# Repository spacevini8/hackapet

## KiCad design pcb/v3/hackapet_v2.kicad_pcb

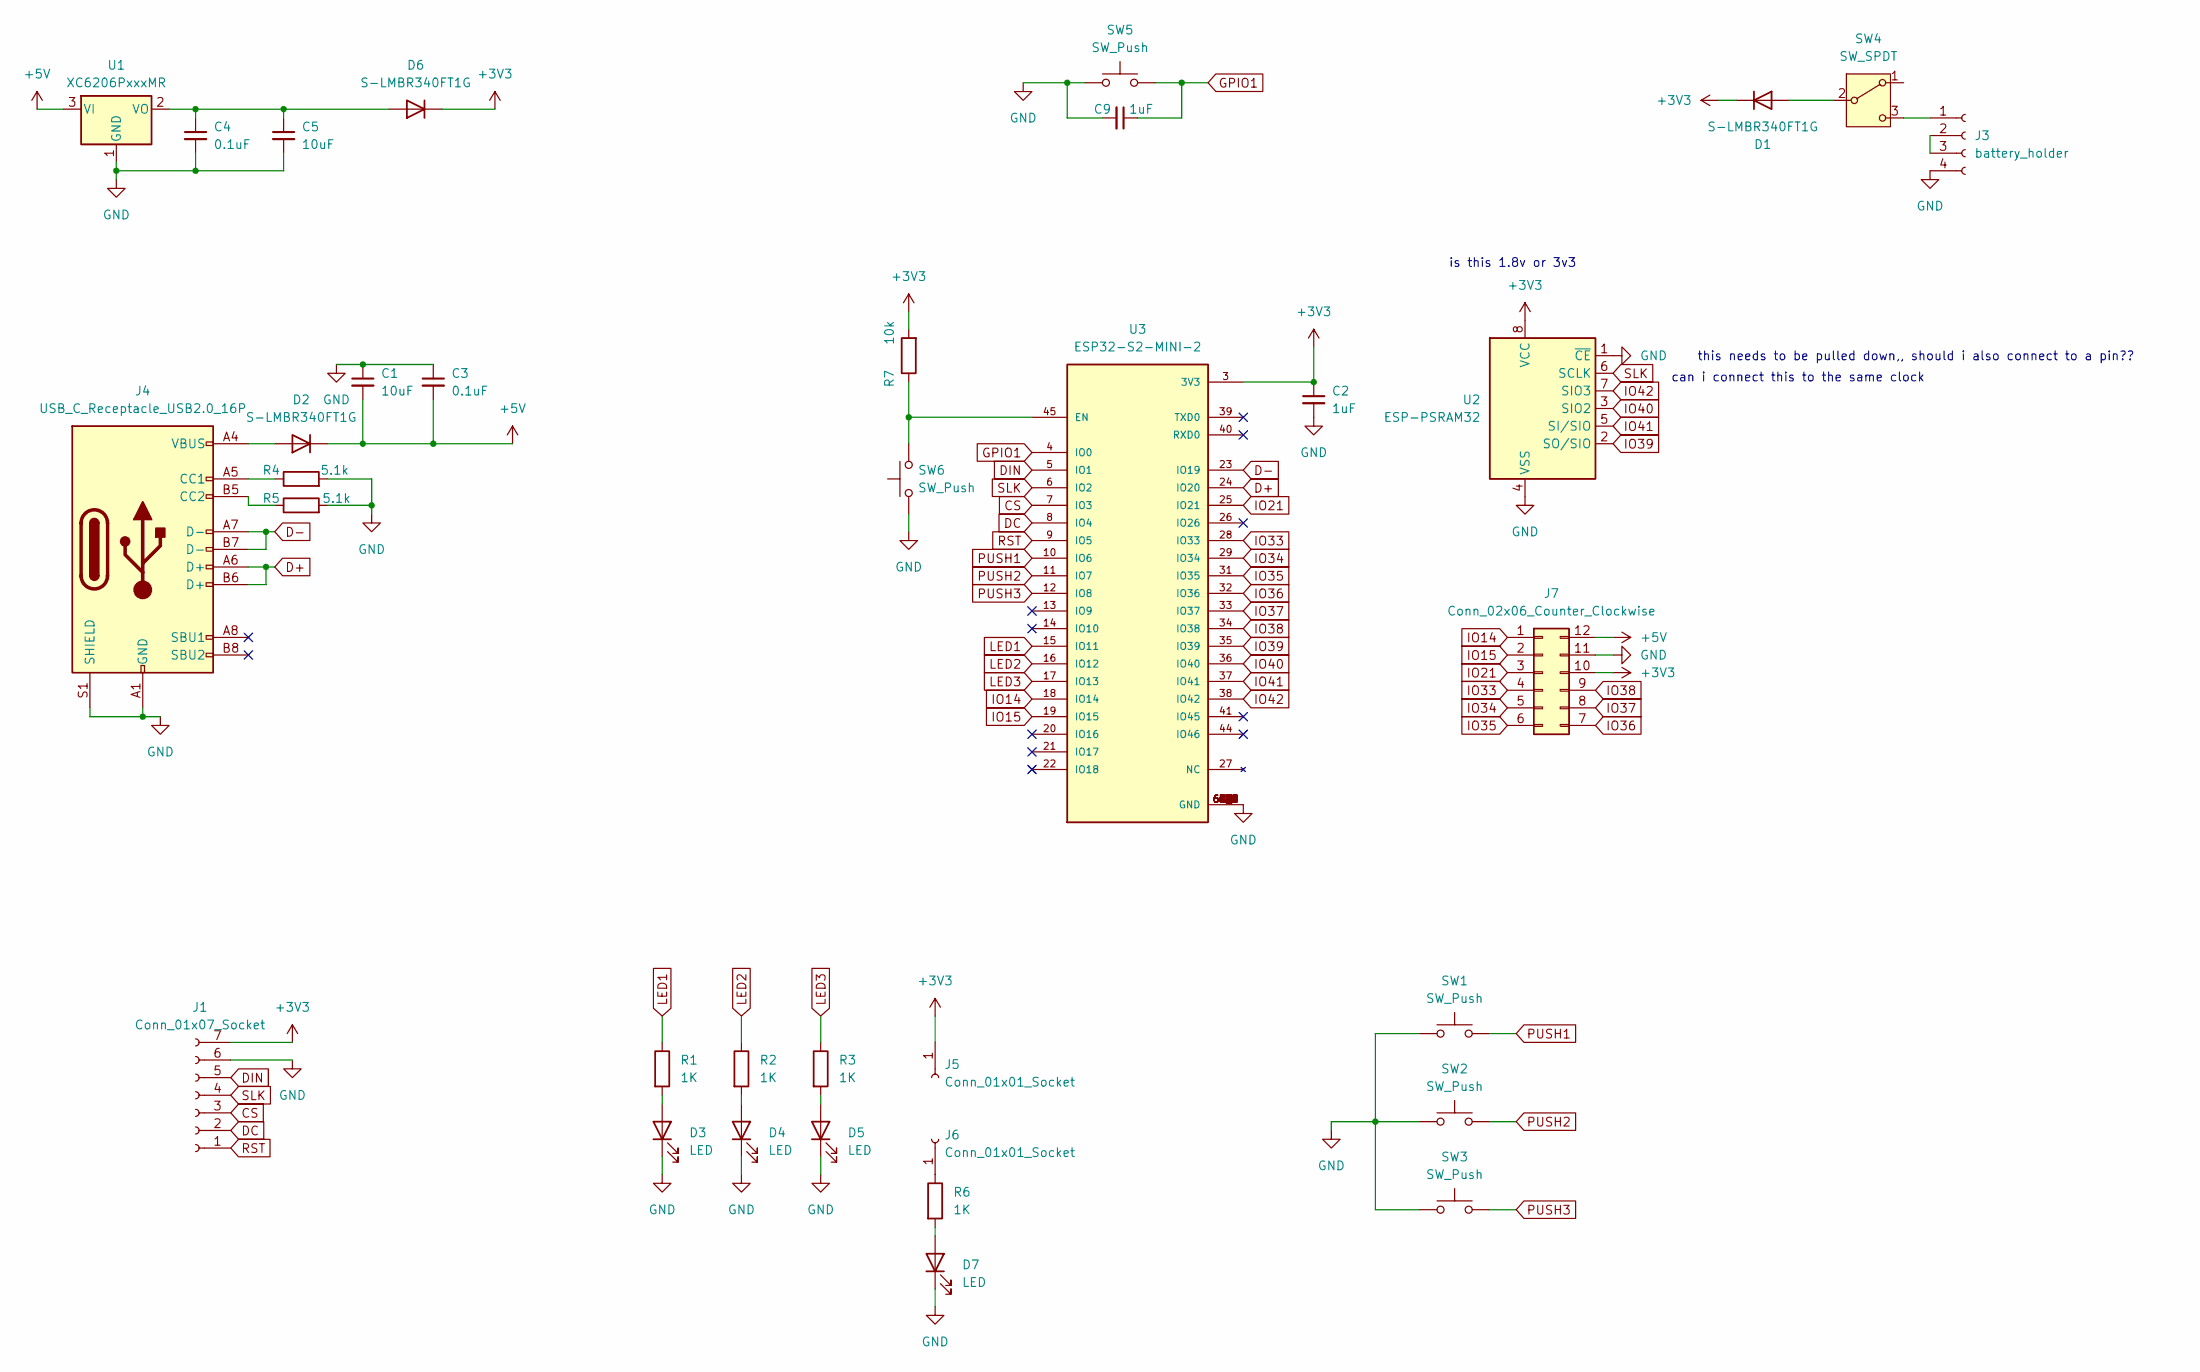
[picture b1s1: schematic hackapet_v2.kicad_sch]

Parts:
C1, C5: 10uF; C_0805_2012Metric; LCSC C5189822
C2, C9: 1uF; C_0805_2012Metric; LCSC C215803
C3, C4: 0.1uF; C_0805_2012Metric; LCSC C28378
D1, D2, D6: S-LMBR340FT1G; D_0805_2012Metric; LCSC C2972823
D3, D4, D5, D7: LED; LED_0805_2012Metric
J1: Conn_01x07_Socket; PinSocket_1x07_P2.54mm_Vertical; LCSC C22438073
J3: battery_holder; 1022_batteryholder
J4: USB_C_Receptacle_USB2.0_16P; USB_C_Receptacle_HCTL_HC-TYPE-C-16P-01A; LCSC C393939
J5, J6: Conn_01x01_Socket; PinSocket_1x01_P2.54mm_Vertical
J7: Conn_02x06_Counter_Clockwise; PinSocket_2x06_P2.54mm_Vertical
R1, R2, R3, R6: 1K; R_0805_2012Metric; LCSC C17513
R4, R5: 5.1k; R_0805_2012Metric; LCSC C104375
R7: 10k; R_0402_1005Metric
SW1, SW2, SW3: SW_Push; SW_Push_1P1T_NO_6x6mm_H9.5mm; LCSC C381038
SW4: SW_SPDT; SW_DPDT_CK_JS202011JCQN; LCSC C221666
SW5: SW_Push; SW_Push_1P1T_XKB_TS-1187A; LCSC C381038
SW6: SW_Push; SW_Push_1P1T_XKB_TS-1187A
U1: XC6206PxxxMR; SOT-23-3
U2: ESP-PSRAM32; SOIC-8_3.9x4.9mm_P1.27mm
U3: ESP32-S2-MINI-2; XCVR_ESP32-S2-MINI-1; PARTREV 1.0; LCSC C3013906

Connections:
+3V3: C2.1, D1.1 (K), D6.1 (K), J1.7, J5.1, J7.10, R7.2, U2.8 (VCC), U3.3 (3V3)
+5V: C1.2, C3.2, D2.1 (K), J7.12, U1.3 (VI)
CS: J1.3, U3.7 (IO3)
D+: J4.A6 (D+), J4.B6 (D+), U3.24 (IO20)
D-: J4.A7 (D-), J4.B7 (D-), U3.23 (IO19)
DC: J1.2, U3.8 (IO4)
DIN: J1.5, U3.5 (IO1)
GND: C1.1, C2.2, C3.1, C4.2, C5.2, C9.2, D3.1 (K), D4.1 (K), D5.1 (K), D7.1 (K), J1.6, J3.4, J4.A1 (GND), J4.A12 (GND), J4.B1 (GND), J4.B12 (GND), J4.S1 (SHIELD), J7.11, R4.2, R5.2, SW1.1, SW2.1, SW3.1, SW5.1, SW6.1, U1.1 (GND), U2.1 (~CE), U2.4 (VSS), U3.1 (GND), U3.2 (GND), U3.30 (GND), U3.42 (GND), U3.43 (GND), U3.46 (GND), U3.47 (GND), U3.48 (GND), U3.49 (GND), U3.50 (GND), U3.51 (GND), U3.52 (GND), U3.53 (GND), U3.54 (GND), U3.55 (GND), U3.56 (GND), U3.57 (GND), U3.58 (GND), U3.59 (GND), U3.60 (GND), U3.61 (GND), U3.61_1 (GND), U3.61_2 (GND), U3.61_3 (GND), U3.61_4 (GND), U3.61_5 (GND), U3.61_6 (GND), U3.61_7 (GND), U3.61_8 (GND), U3.62 (GND), U3.63 (GND), U3.64 (GND), U3.65 (GND)
GPIO1: C9.1, SW5.2, U3.4 (IO0)
IO14: J7.1, U3.18 (IO14)
IO15: J7.2, U3.19 (IO15)
IO21: J7.3, U3.25 (IO21)
IO33: J7.4, U3.28 (IO33)
IO34: J7.5, U3.29 (IO34)
IO35: J7.6, U3.31 (IO35)
IO36: J7.7, U3.32 (IO36)
IO37: J7.8, U3.33 (IO37)
IO38: J7.9, U3.34 (IO38)
IO39: U2.2 (SO/SIO), U3.35 (IO39)
IO40: U2.3 (SIO2), U3.36 (IO40)
IO41: U2.5 (SI/SIO), U3.37 (IO41)
IO42: U2.7 (SIO3), U3.38 (IO42)
LED1: R1.1, U3.15 (IO11)
LED2: R2.1, U3.16 (IO12)
LED3: R3.1, U3.17 (IO13)
unnamed: D1.2 (A), SW4.2 (B)
unnamed: D2.2 (A), J4.A4 (VBUS), J4.A9 (VBUS), J4.B4 (VBUS), J4.B9 (VBUS)
unnamed: D3.2 (A), R1.2
unnamed: D4.2 (A), R2.2
unnamed: D5.2 (A), R3.2
unnamed: C4.1, C5.1, D6.2 (A), U1.2 (VO)
unnamed: D7.2 (A), R6.2
unnamed: J3.1, SW4.3 (C)
unnamed: J3.2, J3.3
unnamed: J4.A5 (CC1), R4.1
unnamed: J4.B5 (CC2), R5.1
unnamed: J6.1, R6.1
unnamed: R7.1, SW6.2, U3.45 (EN)
PUSH1: SW1.2, U3.10 (IO6)
PUSH2: SW2.2, U3.11 (IO7)
PUSH3: SW3.2, U3.12 (IO8)
RST: J1.1, U3.9 (IO5)
SLK: J1.4, U2.6 (SCLK), U3.6 (IO2)

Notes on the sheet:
this needs to be pulled down,, should i also connect to a pin??
can i connect this to the same clock
is this 1.8v or 3v3

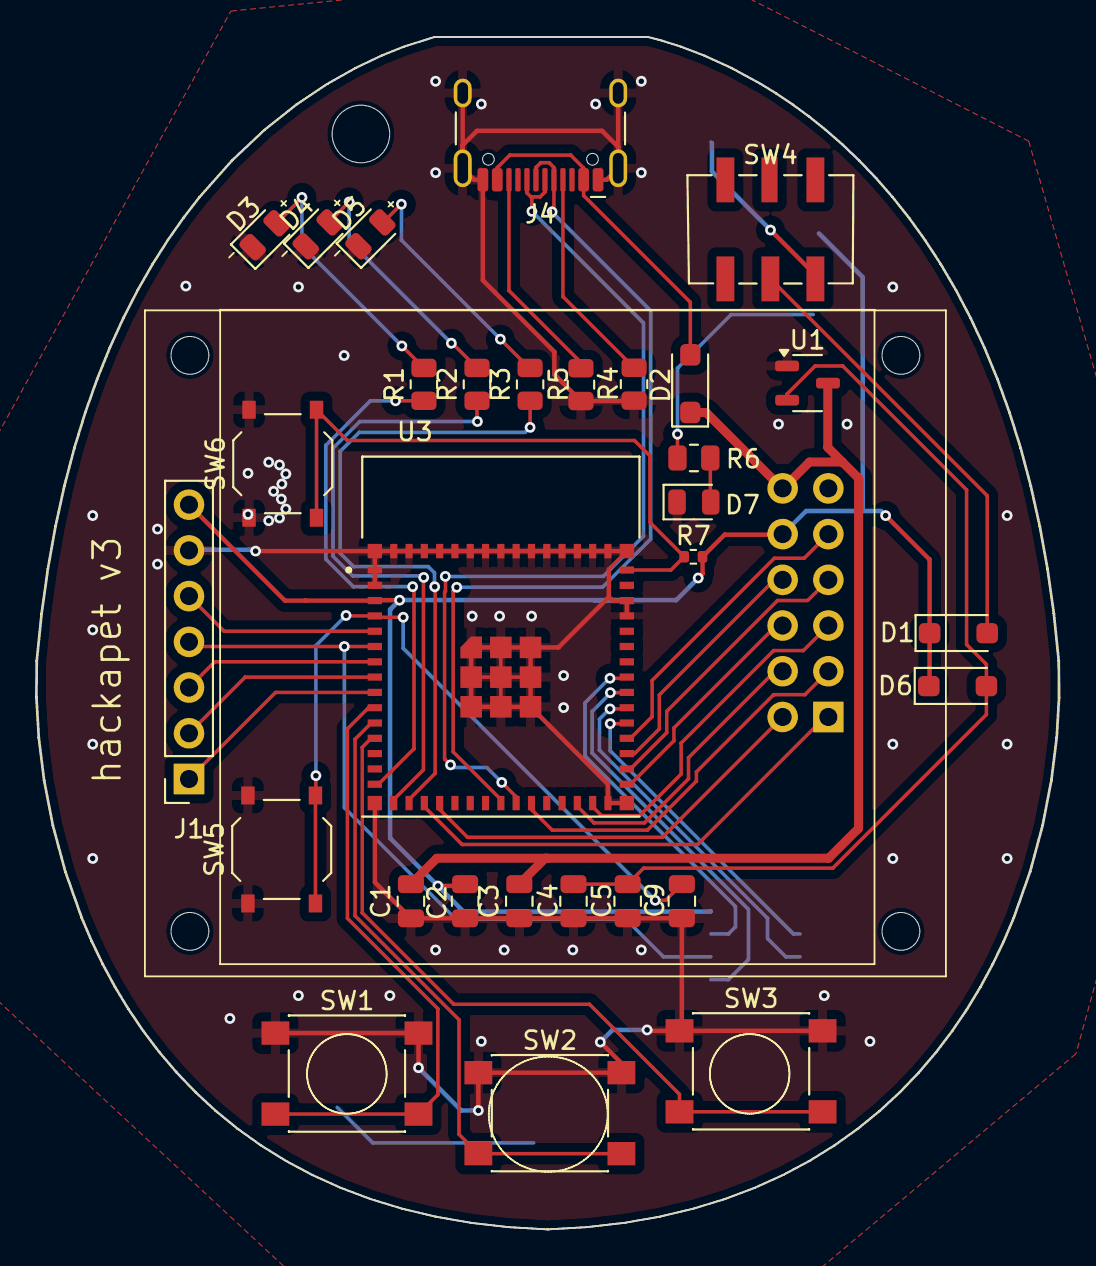
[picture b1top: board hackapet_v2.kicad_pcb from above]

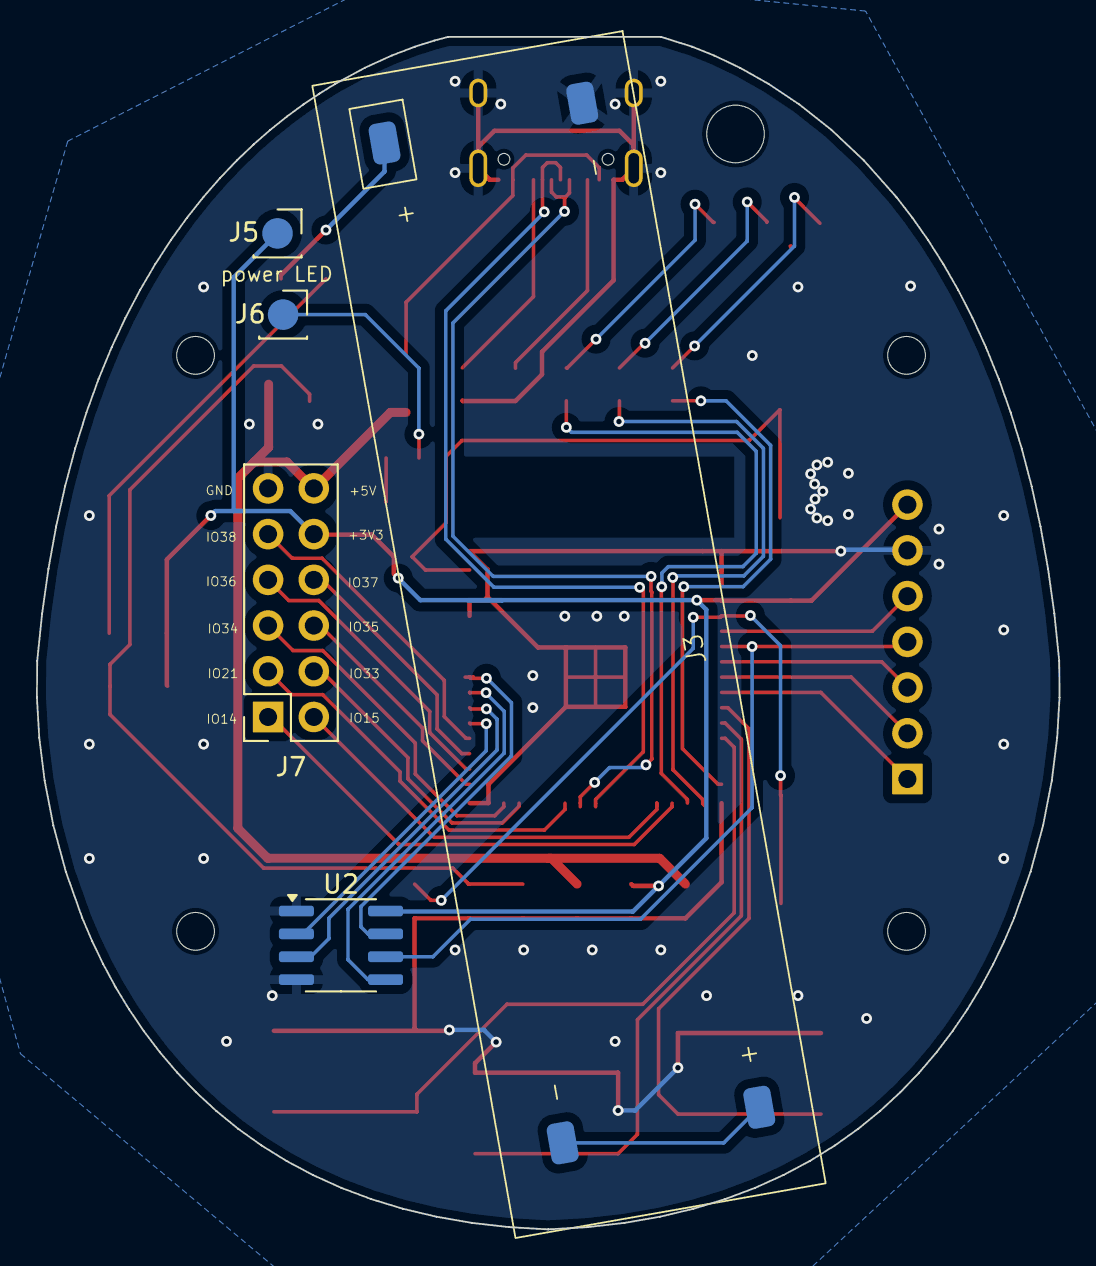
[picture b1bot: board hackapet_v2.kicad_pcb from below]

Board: 2 copper layers, 56.8 x 66.2 mm, 35 parts (5 on the bottom side), 43 nets.

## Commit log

2025-01-19 Create slay or save
2025-01-19 Add files via upload
    added project
2025-01-26 Catch Submission
2025-01-26 Add Glitch Fox: Byte Hunter game
2025-01-27 added requirements.txt
2025-01-28 add cat catch
2025-01-28 teachable blob
2025-01-29 starpet v0.1
2025-01-29 rename to space pet 14
2025-01-29 Add pong clone
2025-01-29 v0.2 added door sprites
2025-01-29 added gitignore
2025-01-29 stops player from going past the left and right walls
2025-01-29 added readme
2025-01-29 update readme 2
2025-01-29 update readme 3
2025-01-29 update readme 4
2025-01-29 add scoring system (prototype) and improve controls in space_pet.py
2025-01-30 WIP: Eeevee
2025-01-30 Add comment and update credits screen
2025-01-30 making an experimental food system
2025-01-30 readme update
2025-01-30 update ball texture and make movement smoother
2025-01-30 Made the base game
    Not super sure I did this right
2025-01-30 fixed a bug in the funny eating moff system fr fr no cap (send help)
2025-01-30 Fixed font error
2025-01-30 Initial Game Commit
    Assets and game code
2025-01-30 Inital Commit
2025-01-30 Added requirements.txt file
2025-01-30 Added basic description and instructions
2025-01-31 fix only 3 burgers spawning (of course it was the one change i didn't test)
2025-01-31 Added death condition anc screen
2025-01-31 Add Game
2025-01-31 add start screen, update end screen text
2025-01-31 Added growth stages
2025-01-31 fixed asset errorj
2025-01-31 Added death, start screen, better bakcground ,and fixed fonts
2025-01-31 finished hunger system, added AME sprites
2025-01-31 added a simple game over system
2025-01-31 added game over system
2025-01-31 not much
2025-01-31 Recommitting Main Code
2025-01-31 Added win condition
2025-02-01 Added heal function and health bar
2025-02-01 added croutonpet
2025-02-01 Added feedback features
    I lowkey think there might be a bug with the arrow and tile collision cuz I swear I pressed the key but I still lost a heart...
2025-02-01 Changed settings and updated readme
2025-02-01 Removed hw_accel flag for compatibility
2025-02-01 upload Your Pocket Arctic Fox game files
2025-02-01 Add files via upload
    that's right, i dont wanna git pull this again
2025-02-01 init commit
2025-02-01 added backgrounds for title and death screens
2025-02-01 door funny, also a dumb error
2025-02-01 added score display system
2025-02-01 hunger and round score counters
2025-02-01 door system near completion, food rebalancing
2025-02-01 started on AME system
2025-02-01 started on AME system 2
2025-02-01 fixed stupid round score bug
2025-02-01 added starvation and AME system
2025-02-01 added randomiser and writing system
2025-02-01 added main
2025-02-01 added singulo and solar
2025-02-01 Breathing animation stuff
2025-02-01 Fixed breathing animation
2025-02-01 Added biscuit sprites
2025-02-01 Background animation
2025-02-02 created requirements.txt
2025-02-02 changed fonts, added text to title and end screen
2025-02-02 added README.md
2025-02-02 add original pixel art + font used
2025-02-02 added score + updated text
2025-02-02 removed unused font
2025-02-02 adjusted food position
2025-02-02 upload aseprite files
2025-02-02 added saikyo sans font, updated food sprites
2025-02-02 most of the game code (I forgot to commit over time)
2025-02-02 resubmission with circuitpython
2025-02-02 Update main.py
    added feedback
2025-02-02 Create temp
2025-02-02 Rename readme.md to README.md
2025-02-02 clarified readme
2025-02-02 update readme and added singularity engine (singulo)
2025-02-02 added solar
2025-02-02 new bitmaps
2025-02-02 update readme, new demo video!
2025-02-02 Create main.py
    submit main.py
2025-02-02 Create a.txt
    temporary file
2025-02-02 upload to github
2025-02-02 Added all of my game files and a README.md file
2025-02-03 Updated code.py
    added bigger stick and meat, made fox react when you feed it/throw sticks at it.
2025-02-03 Create a
2025-02-03 uploaded tris
    :3
2025-02-03 removed .ase files i forgot i left those in there :33
2025-02-03 Create Slime_Train!
2025-02-03 Create bonnies_sweet_buffet
2025-02-03 yessss
2025-02-03 readme and requiremnets
2025-02-03 Added my game
2025-02-03 Zeroed my game
2025-02-03 deleted .idea folder
    oops
2025-02-03 Added KawaiiPet.
2025-02-03 fixed menu overlay issue (a bit jank)
2025-02-03 add colourbounce
2025-02-04 add RocketPPenguin
2025-02-04 Fixed float as intiger error
2025-02-04 Adding Rabeat game
2025-02-04 add my wys demake
2025-02-04 whoops havent update
2025-02-04 Slow down to look better
2025-02-04 Added Smokey Bear Game
2025-02-04 Create blank
2025-02-04 Create placeholder
2025-02-04 Collecting biscuits finally works!
2025-02-04 Added README, sad screen, and hunger and skill levels.
2025-02-04 Finished restart screen
2025-02-04 my game
2025-02-04 fixed a few minor issues with the bmps and deleted some extra files
2025-02-04 Fixed some issues with the code
2025-02-04 add scores
2025-02-04 add readme
2025-02-04 Added Walk Anim, Sad Jax, Start Screen
2025-02-04 game over system finished
2025-02-04 Added night bg
2025-02-04 fixed food game over bug
2025-02-04 I am stoobid
2025-02-04 fixed it, fricken finally
2025-02-04 Fixed the counter issue
    I fixed an issue with the counter resetting after restarting the game. But somehow that created another big with the winning screen not disappearing with restarting.. can you help?
2025-02-04 Added potato animation
2025-02-04 improve bg
2025-02-04 Incressed bar visibility
2025-02-04 animate burger on plate, collision check improvements (combos and can't catch ones below the plate)
2025-02-04 Updated background to increse potato visibility
2025-02-04 Requirements
2025-02-05 Re-adding rabeat
2025-02-05 Changed the beat signs to be clearer
2025-02-05 now uses spritesheets + changed rotation algo
    now loads from spritesheets instead of each sprite slice having a seperate file, plus rotation algorithm changed from inverse mapping to one using skews to hopefully speed it up although now theres m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
2025-02-05 Update game.py
    it works perfectly fine now !! :D
2025-02-05 Bugs now show up on screen
2025-02-05 added try except statment for hw acceleration
2025-02-05 Added future work to readme
2025-02-06 Updated requirements.txt
2025-02-06 Added read me
2025-02-06 add usage instructions
2025-02-06 Update README.md
    added instructions :)
2025-02-06 Update main.py
    fixed font errors
2025-02-07 add ball animations and slightly change paddle sprite
2025-02-07 Removed .idea again
2025-02-07 remove submodule
    This reverts commit 51531baa2b32e03427804785476c6c62be1c4e15.
2025-02-07 add files
2025-02-08 Add files via upload
    improved animation, hopefully better pixel density?
2025-02-09 remove nix :(
2025-02-09 update pyproject
2025-02-09 Added bear outline, improved labels, countdown timer, fixed removal logic
2025-02-09 Added Start Screen
2025-02-10 added game bar and a droopy tail when she's hungry. To fill the game bar, play 4 games (which will make her turn golden). Every two minutes, a bar from the game bar will be removed as she gets bored.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
2025-02-14 Colors and spinning
2025-02-14 add BLUE
2025-02-14 Added game over menu and a dangerous sword
2025-02-14 Made gameover menu and other minor changes
2025-02-14 Remove scale param bc the standard ptgamedisplay doesn't have it
    im using the cyrillli fork but they said remove the nix packages so it would be getting the one from pypi
2025-02-15 FINAL FINAL VERSION.. promise
    -_-
2025-02-15 Adding Art
2025-02-15 Rename Bonnie's Sweet Buffet Art.png to Art.png
2025-02-16 Backtrack - Start screen and leaving the screen + README
2025-02-16 I'm giving up lol
2025-02-16 Add files via upload
    fixed animations
2025-02-24 add restart and center
2025-02-24 add changes from main repo
2025-02-27 added initial ver of v3
2025-03-04 added reference folder, gitignore on pcb
2025-03-05 moved batt to 3v3 regulator b/c no buck converter
2025-03-19 updated board
2025-04-23 general refactor
2025-04-23 other stuff
